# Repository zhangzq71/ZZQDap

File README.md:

# ZZQDap
ZZQ's CMSIS-DAP project.

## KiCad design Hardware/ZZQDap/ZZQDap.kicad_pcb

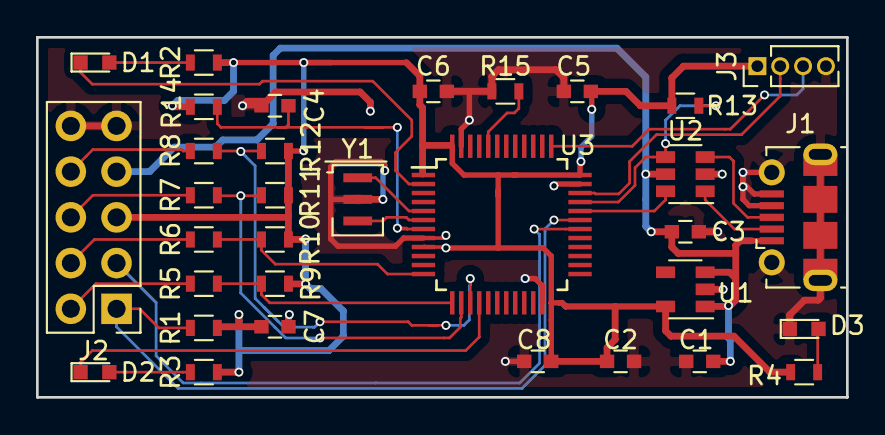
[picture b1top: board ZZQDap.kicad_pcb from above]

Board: 2 copper layers, 45.0 x 20.0 mm, 33 parts (0 on the bottom side), 28 nets.

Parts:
C1, C2: 1uF; C_0603
C3, C4, C5, C6, C7, C8: 0.1uF; C_0603
D1, D2, D3: LED; LED_0603
J1: USB_B_Micro; USB_Micro-B_Molex-105017-0001
J2: Conn_02x05_Odd_Even; Pin_Header_Straight_2x05_Pitch2.54mm
J3: Conn_01x04; Pin_Header_Straight_1x04_Pitch1.27mm
R1, R9, R10, R11, R12, R14, R15: 10K; R_0603
R2, R3, R4: 1K; R_0603
R5, R6, R7, R8: 22R; R_0603
R13: 1.5K; R_0603
U1: SPX3819M5-L-3-3; SOT-23-5
U2: USBLC6-2SC6; SOT-23-6
U3: STM32F103CBTx; LQFP-48_7x7mm_Pitch0.5mm
Y1: 8MHz; Resonator_SMD_muRata

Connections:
+3V3: C2.1, C5.1, C6.1, C7.1, C8.1, J2.5, J3.1, R1.2, R2.2, R3.2, R4.2, R9.2, R10.2, R11.2, R12.2, R13.2, R14.2, U1.5, U3.1, U3.9, U3.24, U3.36, U3.48
+5V: C1.1, C3.1, J1.1, J2.7, U1.1, U1.3, U2.5
/DAP_RESET: R6.2, R10.1, U3.12
/DAP_RX: J2.1, R1.1, U3.31
/DAP_SWCLK: R8.2, R12.1, U3.15
/DAP_SWDIO: R7.2, R11.1, U3.14
/DAP_SWO/TDO: R5.2, R9.1, U3.13
/DAP_TX: J2.3, U3.30
/STATUS_1: D1.1, U3.2
/STATUS_2: D2.1, U3.16
/SWCLK: J3.3, U3.37
/SWDIO: J3.2, U3.34
/USB_DM: U2.6, U3.32
/USB_PM: R13.1, U2.4, U3.33
GND: C1.2, C2.2, C3.2, C4.2, C5.2, C6.2, C7.2, C8.2, D3.1, J1.4, J1.5, J1.6, J2.9, J2.10, J3.4, R15.1, U1.2, U2.2, U3.8, U3.23, U3.35, U3.47, Y1.3
unnamed: C4.1, R14.1, U3.7
unnamed: D1.2, R2.1
unnamed: D2.2, R3.1
unnamed: D3.2, R4.1
unnamed: J1.2, U2.1
unnamed: J1.3, U2.3
unnamed: J2.2, R5.1
unnamed: J2.4, R6.1
unnamed: J2.6, R7.1
unnamed: J2.8, R8.1
unnamed: R15.2, U3.44
unnamed: U3.5, Y1.1
unnamed: U3.6, Y1.2

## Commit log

2018-04-11 add hardware design
2018-04-11 add Firmware
2018-04-11 it is version 1
2020-12-03 doc: Updated docs
